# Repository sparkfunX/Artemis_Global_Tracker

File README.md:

# Artemis Global Tracker

An open source global satellite tracker utilising the [SparkFun Artemis module](https://www.sparkfun.com/products/15484),
[Iridium 9603N satellite transceiver](https://www.iridium.com/products/iridium-9603/) and [u-blox ZOE-M8Q GNSS](https://www.u-blox.com/en/product/zoe-m8-series).

[*SparkX Artemis Global Tracker (SPX-16469)*](https://www.sparkfun.com/products/16469)

[*SparkX Artemis Global Tracker (SPX-16469)*](https://www.sparkfun.com/products/16469)

## Retired Product

The SparkX Artemis Global Tracker (SPX-16469) has been replaced by the [SparkFun Artemis Global Tracker (WRL-18712)](https://www.sparkfun.com/products/18712).

## Repository Contents

- **/Documentation** - Documentation for the hardware and the full GlobalTracker example
- **/Hardware** - Eagle PCB, SCH and LBR design files
- **/Software** - Arduino examples
- **/Tools** - Tools to help: configure the full GlobalTracker example via USB or remotely via Iridium messaging; and track and map its position
- **/binaries** - binary files for the examples which you can upload using the [Artemis Firmware Upload GUI](https://github.com/sparkfun/Artemis-Firmware-Upload-GUI) instead of the Arduino IDE
- **LICENSE.md** contains the licence information

## Documentation

- [Hardware overview](Documentation/Hardware_Overview/README.md): an overview of the hardware
- The Artemis pin allocation is summarised [here](Documentation/Hardware_Overview/ARTEMIS_PINS.md)
- [Message Format](Documentation/Message_Format/README.md): a definition of the message format and fields (both binary and text) for the full GlobalTracker example
- [GlobalTracker FAQs](Documentation/GlobalTracker_FAQs/README.md): information to help you operate and configure the AGT

## License Information

This product is _**open source**_!

Please review the LICENSE.md file for license information.

If you have any questions or concerns on licensing, please contact technical support on our [SparkFun forums](https://forum.sparkfun.com/viewforum.php?f=123).

Distributed as-is; no warranty is given.

- Your friends at SparkFun.

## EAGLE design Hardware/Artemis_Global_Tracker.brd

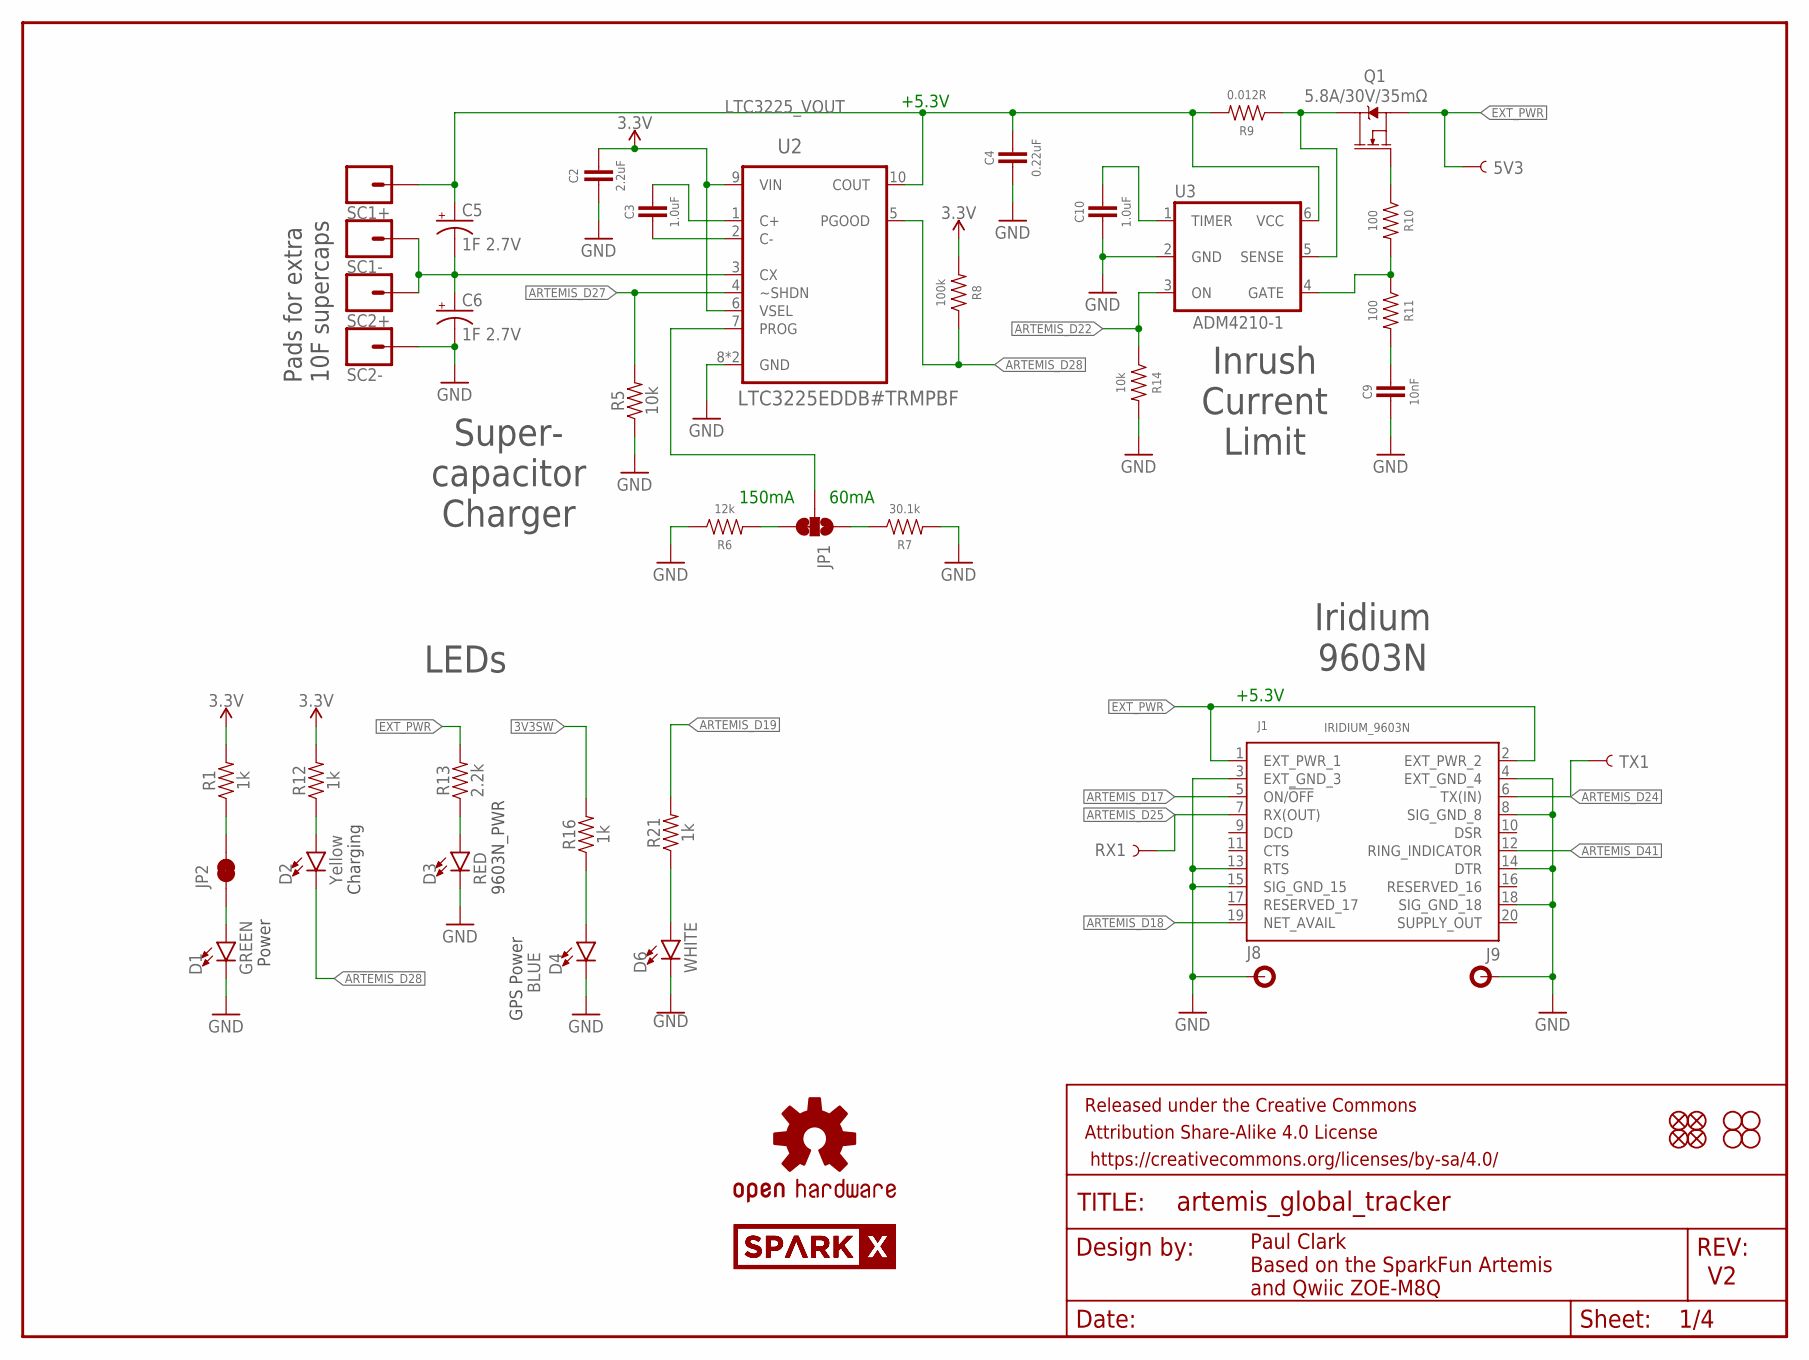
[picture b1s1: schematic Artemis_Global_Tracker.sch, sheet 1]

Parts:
5V3: TEST-POINT3X5; PAD.03X.05
C2: 2.2uF; 0603
C3, C10: 1.0uF; 0603
C4: 0.22uF; 0603
C5, C6: 1F 2.7V; CPOL-RADIAL-1F-2.7V
C9: 10nF; 0603
D1: GREEN; LED-0603
D2: Yellow; LED-0603
D3: RED; LED-0603
D4: BLUE; LED-0603
D6: WHITE; LED-0603
FRAME1: FRAME-LETTER; CREATIVE_COMMONS
J1: IRIDIUM_9603N
J8, J9: STANDOFFS_M2X0.4_STEEL_6MM; STANDOFF_M2X0.4
JP1: JUMPER-SMT_3_1-NC_TRACE_SILK; SMT-JUMPER_3_1-NC_TRACE_SILK
JP2: JUMPER-SMT_2_NC_TRACE_SILK; SMT-JUMPER_2_NC_TRACE_SILK
JP7, JP8, JP13, JP14: FIDUCIAL1X2; FIDUCIAL-1X2
JP9, JP10, JP11, JP12: STAND-OFF
LOGO4: OSHW-LOGOMINI; OSHW-LOGO-MINI
Q1: 5.8A/30V/35mΩ; SOT23-3
R1, R12, R16, R21: 1k; 0603
R5, R14: 10k; 0603
R6: 12k; 0603
R7: 30.1k; 0603
R8: 100k; 0603
R9: 0.012R; 0603
R10, R11: 100; 0603
R13: 2.2k; 0603
RX1: TEST-POINT3X5; PAD.03X.05
SC1+, SC1-, SC2+, SC2-: CONN_01PTH_NO_SILK_YES_STOP; 1X01_NO_SILK
SPARKX1, SPARKX2: SPARKX-LOGO4; SPARKX-MEDIUM
TX1: TEST-POINT3X5; PAD.03X.05
U2: LTC3225EDDB#TRMPBF; DFN300X200-10L
U3: ADM4210-1; TSOT6

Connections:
3.3V: C2.1, R1.2, R8.2, R12.2, U2.6 (VSEL), U2.9 (VIN); also elsewhere on the board
3V3SW: R16.2; also elsewhere on the board
ARTEMIS_D17: J1.5 (ON/!OFF!); also elsewhere on the board
ARTEMIS_D18: J1.19 (NET_AVAIL); also elsewhere on the board
ARTEMIS_D19: R21.2; also elsewhere on the board
ARTEMIS_D22: R14.1, U3.3 (ON); also elsewhere on the board
ARTEMIS_D24: J1.6 (TX(IN)), TX1.P$1; also elsewhere on the board
ARTEMIS_D25: J1.7 (RX(OUT)), RX1.P$1; also elsewhere on the board
ARTEMIS_D27: R5.2, U2.4 (~SHDN); also elsewhere on the board
ARTEMIS_D28: D2.C, R8.1, U2.5 (PGOOD); also elsewhere on the board
ARTEMIS_D41: J1.12 (RING_INDICATOR); also elsewhere on the board
EXT_PWR: 5V3.P$1, J1.1 (EXT_PWR_1), J1.2 (EXT_PWR_2), Q1.2 (S), R13.2; also elsewhere on the board
GND: C2.2, C4.2, C6.-, C9.2, C10.2, D1.C, D3.C, D4.C, D6.C, J1.3 (EXT_GND_3), J1.4 (EXT_GND_4), J1.8 (SIG_GND_8), J1.13 (RTS), J1.14 (DTR), J1.15 (SIG_GND_15), J1.18 (SIG_GND_18), J8.1, J9.1, R5.1, R6.1, R7.2, R14.2, SC2-.1, U2.8 (GND), U2.11 (GND), U3.2 (GND); also elsewhere on the board
LTC3225_VOUT: C4.1, C5.+, R9.2, SC1+.1, U2.10 (COUT), U3.6 (VCC)
unnamed: C5.-, C6.+, SC1-.1, SC2+.1, U2.3 (CX)
unnamed: JP1.3, R6.2
unnamed: JP2.2, R1.1
unnamed: JP1.1, R7.1
unnamed: D2.A, R12.1
unnamed: D3.A, R13.1
unnamed: Q1.3 (D), R9.1, U3.5 (SENSE)
unnamed: C3.2, U2.2 (C-)
unnamed: C3.1, U2.1 (C+)
unnamed: JP1.2, U2.7 (PROG)
unnamed: Q1.1 (G), R10.1
unnamed: R10.2, R11.1, U3.4 (GATE)
unnamed: C9.1, R11.2
unnamed: C10.1, U3.1 (TIMER)
unnamed: D4.A, R16.1
unnamed: D1.A, JP2.1
unnamed: D6.A, R21.1

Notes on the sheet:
Paul Clark Based on the SparkFun Artemis and Qwiic ZOE-M8Q
Power
+5.3V
150mA
60mA
Pads for extra 10F supercaps
Super- capacitor Charger
Charging
9603N_PWR
Iridium 9603N
LEDs
Inrush Current Limit
GPS Power

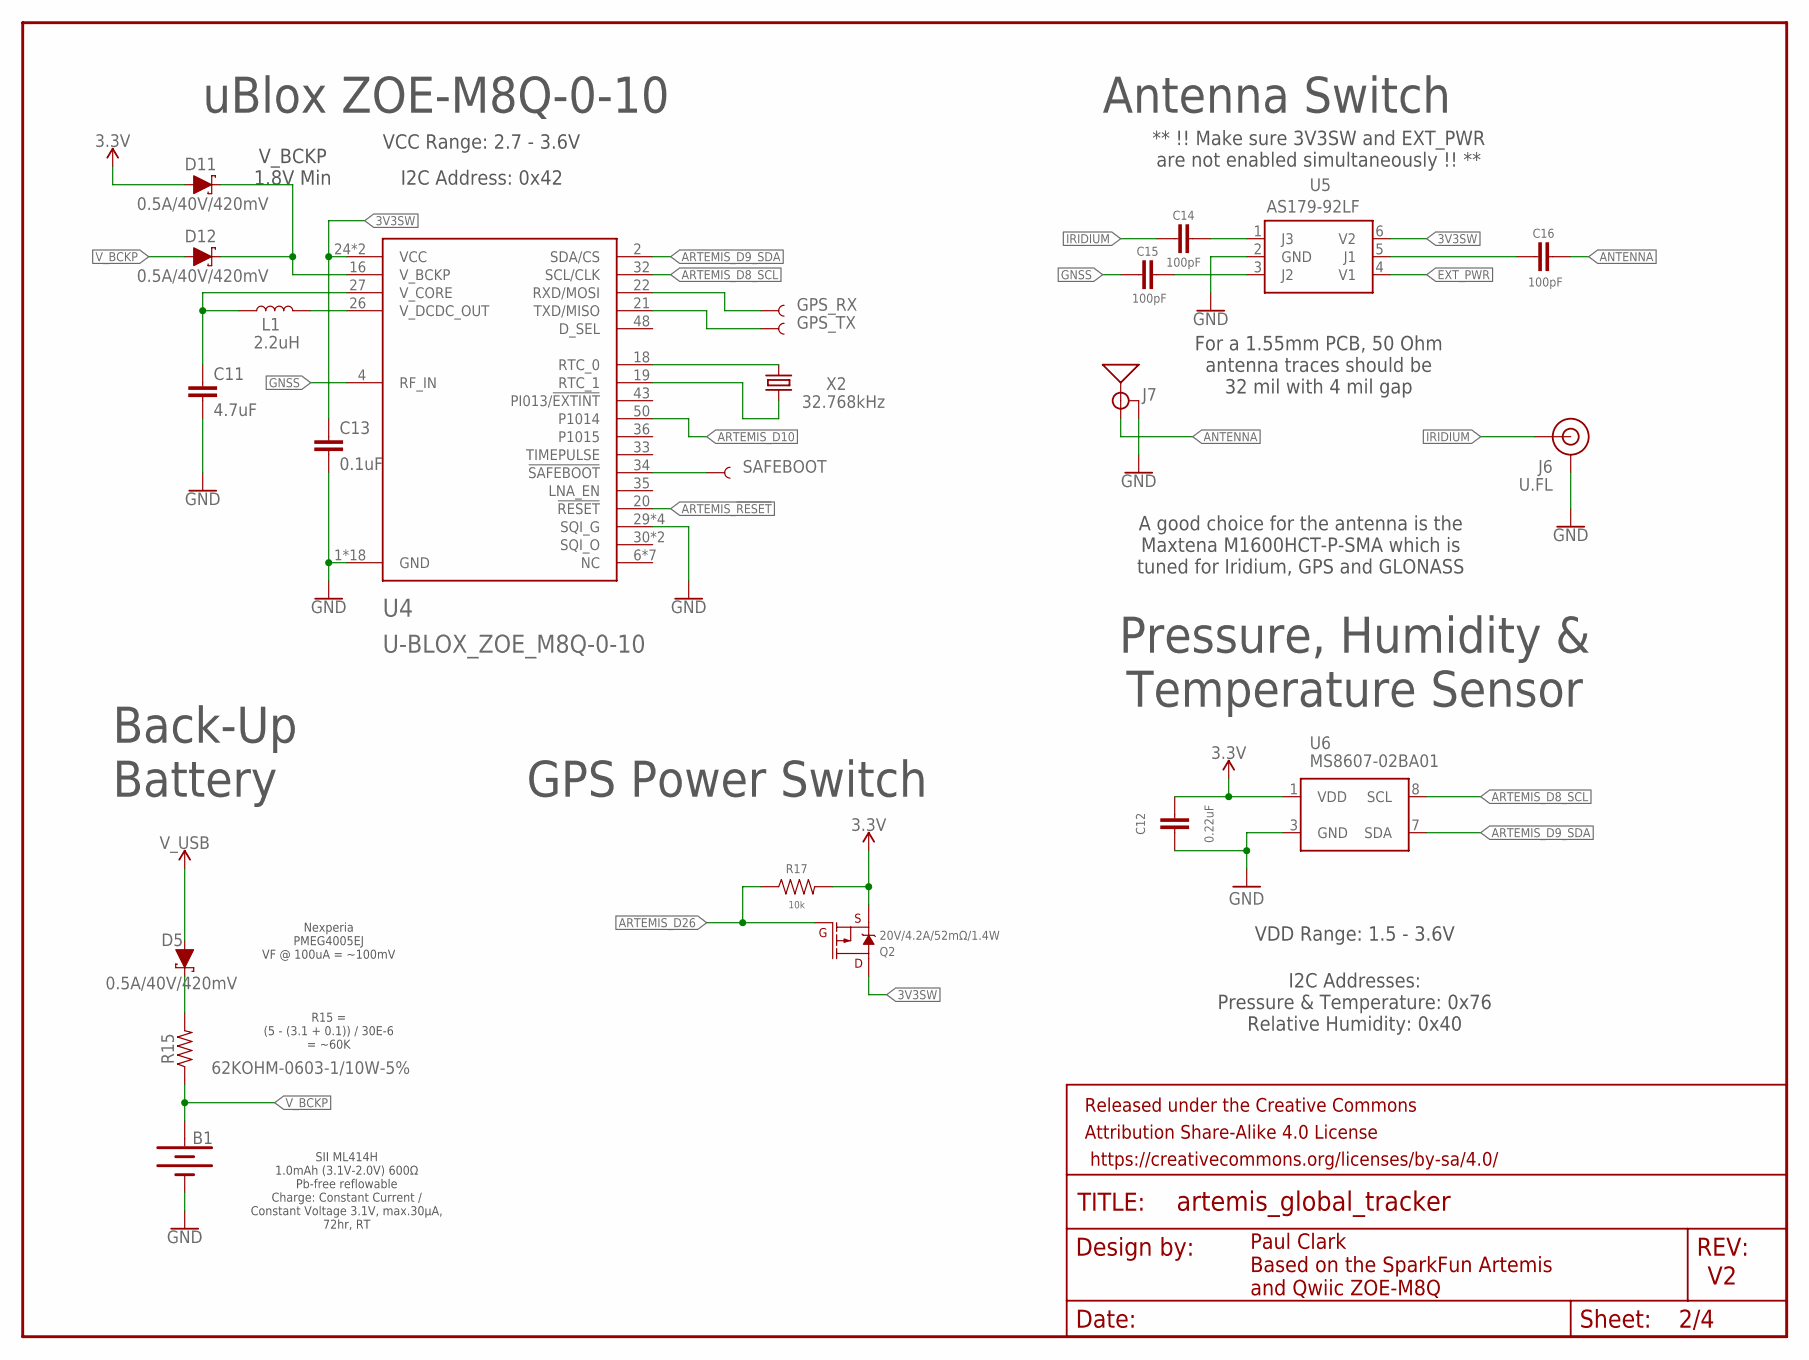
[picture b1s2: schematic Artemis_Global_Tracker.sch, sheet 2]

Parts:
B1: ML414H_IV01E_BATTERY; ML414H_IV01E
C11: 4.7uF; 0603
C12: 0.22uF; 0603
C13: 0.1uF; 0603
C14, C15, C16: 100pF; 0603
D5, D11, D12: 0.5A/40V/420mV; SOD-323
FRAME2: FRAME-LETTER; CREATIVE_COMMONS
GPS_RX: TEST-POINT3X5; PAD.03X.05
GPS_TX: TEST-POINT3X5; PAD.03X.05
J6: U.FL
J7: ANTENNA-GROUNDEDEDGE_SMA; SMA-EDGE
L1: 2.2uH; 0806
Q2: 20V/4.2A/52mΩ/1.4W; SOT23-3
R15: 62KOHM-0603-1/10W-5%; 0603
R17: 10k; 0603
SAFEBOOT: TEST-POINT3X5; PAD.03X.05
U4: U-BLOX_ZOE_M8Q-0-10; UBLOX_ZOE_M8-0-10
U5: AS179-92LF; SOT65P220X100-6N
U6: MS8607-02BA01
X2: 32.768kHz; CRYSTAL-SMD-3.2X1.5MM

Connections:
3.3V: C12.1, D11.A, Q2.2 (S), R17.2, U6.1 (VDD); also elsewhere on the board
3V3SW: C13.1, Q2.3 (D), U4.24 (VCC), U4.25 (VCC), U5.6 (V2); also elsewhere on the board
ANTENNA: C16.1, J7.SIG (SIGNAL)
ARTEMIS_!RESET: U4.20 (!RESET); also elsewhere on the board
ARTEMIS_D8_SCL: U4.32 (SCL/CLK), U6.8 (SCL); also elsewhere on the board
ARTEMIS_D9_SDA: U4.2 (SDA/CS), U6.7 (SDA); also elsewhere on the board
ARTEMIS_D10: U4.50 (P1014); also elsewhere on the board
ARTEMIS_D26: Q2.1 (G), R17.1; also elsewhere on the board
EXT_PWR: U5.4 (V1); also elsewhere on the board
GND: B1.-, C11.2, C12.2, C13.2, J6.1 (GND), J6.2 (GND), J7.GND@0 (GND), J7.GND@1 (GND), J7.GND@2 (GND), J7.GND@3 (GND), U4.1 (GND), U4.3 (GND), U4.5 (GND), U4.7 (GND), U4.8 (GND), U4.9 (GND), U4.10 (GND), U4.11 (GND), U4.12 (GND), U4.17 (GND), U4.23 (GND), U4.29 (SQI_G), U4.31 (SQI_G), U4.37 (GND), U4.38 (GND), U4.39 (GND), U4.40 (GND), U4.41 (GND), U4.44 (GND), U4.46 (SQI_G), U4.47 (SQI_G), U4.49 (GND), U5.2 (GND), U6.3 (GND); also elsewhere on the board
GNSS: C15.2, U4.4 (RF_IN)
IRIDIUM: C14.2, J6.FEED (SIGNAL)
unnamed: L1.2, U4.26 (V_DCDC_OUT)
unnamed: C11.1, L1.1, U4.27 (V_CORE)
unnamed: U4.18 (RTC_0), X2.P$2 (2)
unnamed: U4.19 (RTC_1), X2.P$1 (1)
unnamed: D5.C, R15.2
unnamed: D11.C, D12.C, U4.16 (V_BCKP)
unnamed: SAFEBOOT.P$1, U4.34 (!SAFEBOOT)
unnamed: GPS_RX.P$1, U4.22 (RXD/MOSI)
unnamed: GPS_TX.P$1, U4.21 (TXD/MISO)
unnamed: C14.1, U5.1 (J3)
unnamed: C15.1, U5.3 (J2)
unnamed: C16.2, U5.5 (J1)
V_BCKP: B1.+, D12.A, R15.1
V_USB: D5.A; also elsewhere on the board

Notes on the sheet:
Paul Clark Based on the SparkFun Artemis and Qwiic ZOE-M8Q
uBlox ZOE-M8Q-0-10
Back-Up Battery
Antenna Switch
SII ML414H 1.0mAh (3.1V-2.0V) 600Ω Pb-free reflowable Charge: Constant Current / Constant Voltage 3.1V, max.30μA, 72hr, RT
VCC Range: 2.7 - 3.6V
I2C Address: 0x42
GPS Power Switch
Pressure, Humidity & Temperature Sensor
VDD Range: 1.5 - 3.6V
I2C Addresses: Pressure & Temperature: 0x76 Relative Humidity: 0x40
** !! Make sure 3V3SW and EXT_PWR are not enabled simultaneously !! **
A good choice for the antenna is the Maxtena M1600HCT-P-SMA which is tuned for Iridium, GPS and GLONASS
For a 1.55mm PCB, 50 Ohm antenna traces should be 32 mil with 4 mil gap
Nexperia PMEG4005EJ VF @ 100uA = ~100mV
R15 = (5 - (3.1 + 0.1)) / 30E-6 = ~60K
V_BCKP 1.8V Min

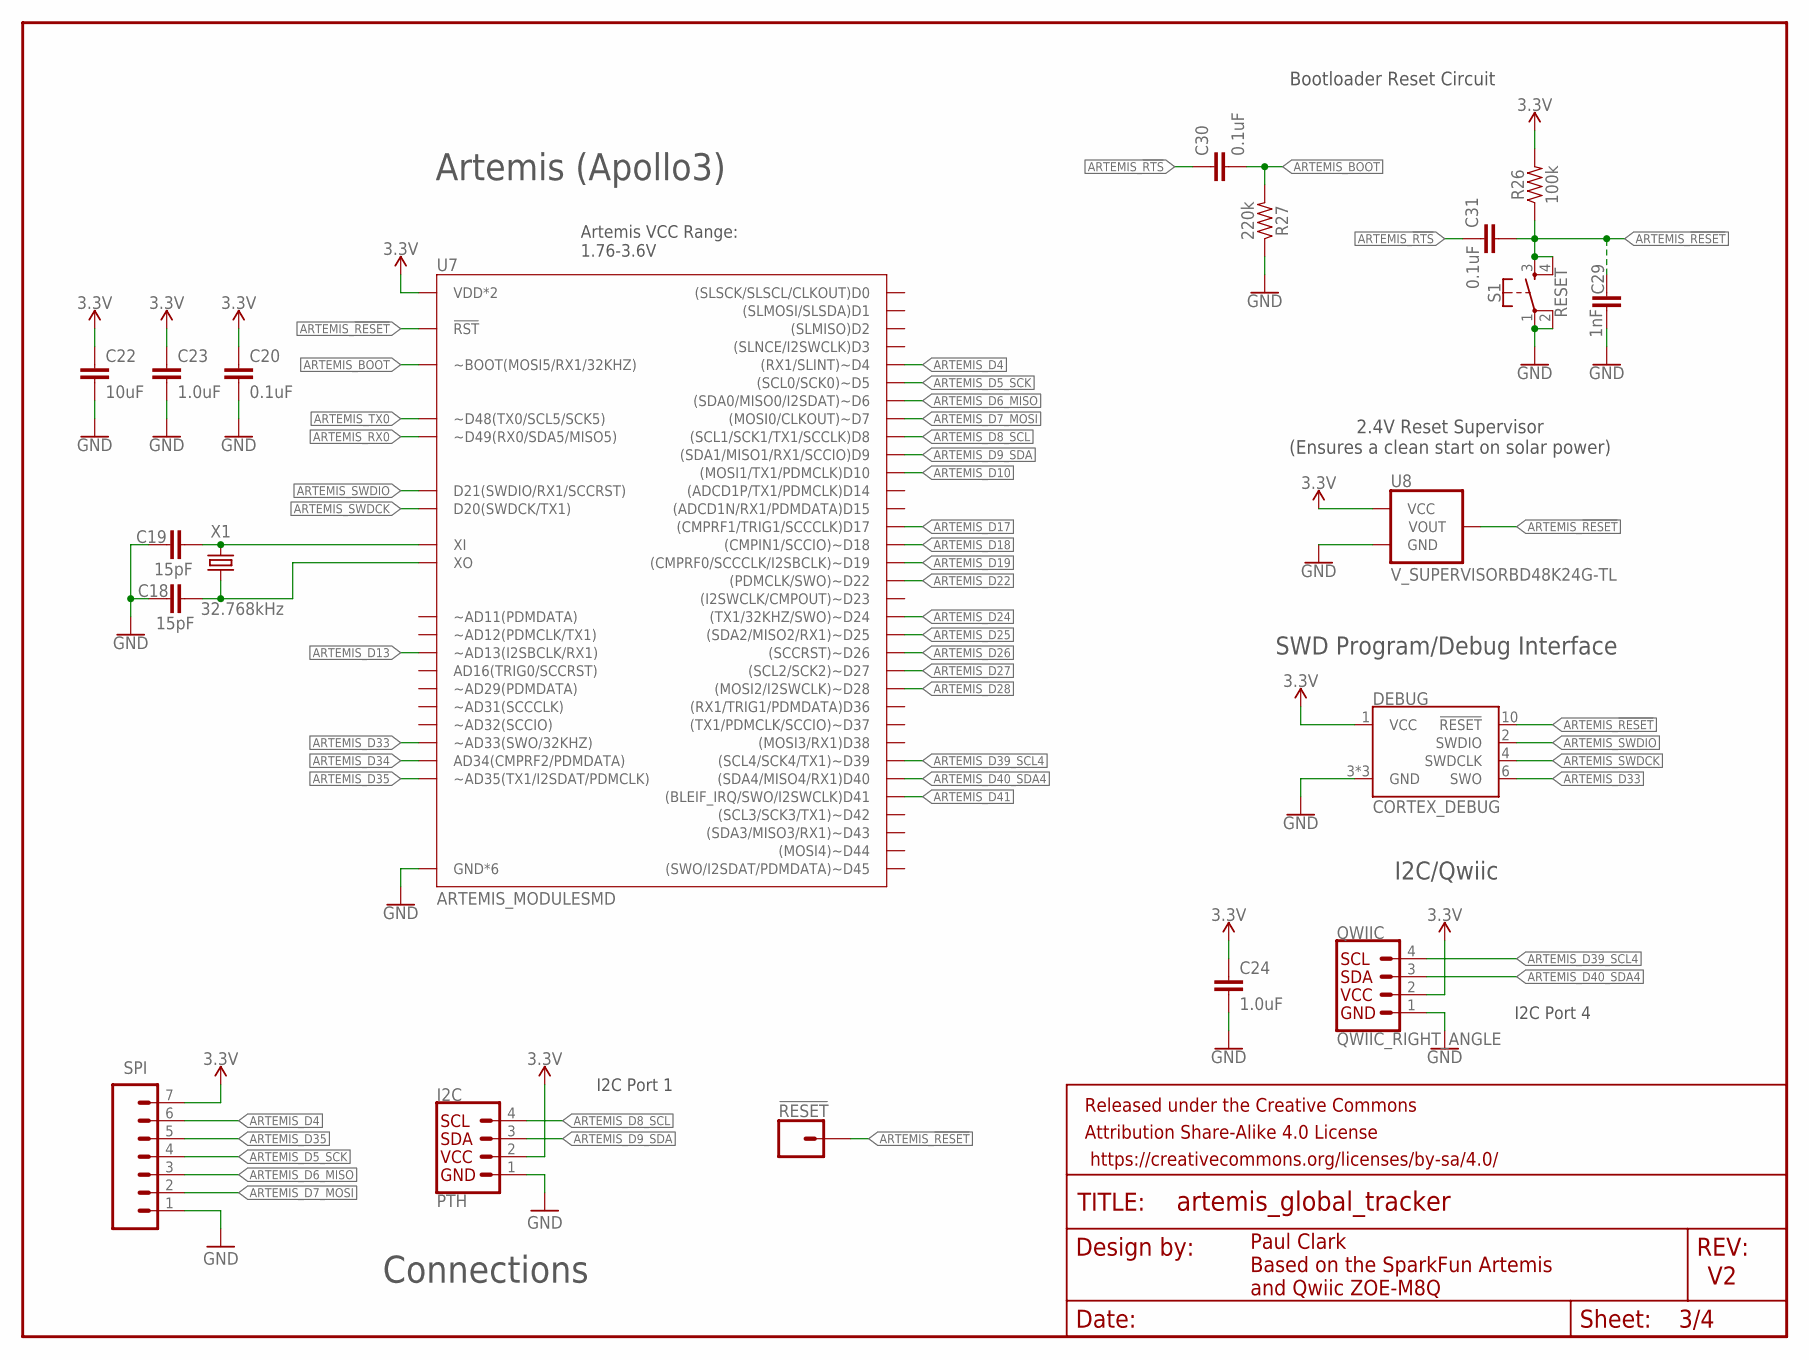
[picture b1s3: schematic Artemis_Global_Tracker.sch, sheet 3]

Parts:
!RESET: CONN_01PTH_NO_SILK_YES_STOP; 1X01_NO_SILK
C18, C19: 15pF; 0603
C20, C30, C31: 0.1uF; 0603
C22: 10uF; 0603
C23, C24: 1.0uF; 0603
C29: 1nF; 0603
DEBUG: CORTEX_DEBUG; 2X5-PTH-1.27MM-NO_SILK
FRAME3: FRAME-LETTER; CREATIVE_COMMONS
I2C: PTH; 1X04_NO_SILK
QWIIC: QWIIC_RIGHT_ANGLE; JST04_1MM_RA
R26: 100k; 0603
R27: 220k; 0603
S1: RESET; TACTILE_SWITCH_SMD_5.2MM
SPI: CONN_07NO_SILK; 1X07_NO_SILK
U7: ARTEMIS_MODULESMD; ARTEMIS_FP
U8: V_SUPERVISORBD48K24G-TL; SSOP3
X1: 32.768kHz; CRYSTAL-SMD-3.2X1.5MM

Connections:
3.3V: C20.2, C22.1, C23.1, C24.1, DEBUG.1 (VCC), I2C.2, QWIIC.2, R26.2, SPI.7, U7.VDD@36 (VDD*2), U7.VDD@37 (VDD*2), U8.3 (VCC); also elsewhere on the board
ARTEMIS_!RESET: !RESET.1, C29.1, C31.2, DEBUG.10 (!RESET), R26.1, S1.3, S1.4, U7.~RST (!RST), U8.2 (VOUT); also elsewhere on the board
ARTEMIS_!RTS!: C30.1, C31.1; also elsewhere on the board
ARTEMIS_BOOT: C30.2, R27.2, U7.BOOT (~BOOT(MOSI5/RX1/32KHZ))
ARTEMIS_D4: SPI.6, U7.~D4 ((RX1/SLINT)~D4)
ARTEMIS_D5_SCK: SPI.4, U7.~D5 ((SCL0/SCK0)~D5)
ARTEMIS_D6_MISO: SPI.3, U7.~D6 ((SDA0/MISO0/I2SDAT)~D6)
ARTEMIS_D7_MOSI: SPI.2, U7.D7 ((MOSI0/CLKOUT)~D7)
ARTEMIS_D8_SCL: I2C.4, U7.D8 ((SCL1/SCK1/TX1/SCCLK)D8); also elsewhere on the board
ARTEMIS_D9_SDA: I2C.3, U7.D9 ((SDA1/MISO1/RX1/SCCIO)D9); also elsewhere on the board
ARTEMIS_D10: U7.D10 ((MOSI1/TX1/PDMCLK)D10); also elsewhere on the board
ARTEMIS_D13: U7.~AD13 (~AD13(I2SBCLK/RX1)); also elsewhere on the board
ARTEMIS_D17: U7.D17 ((CMPRF1/TRIG1/SCCCLK)D17); also elsewhere on the board
ARTEMIS_D18: U7.~D18 ((CMPIN1/SCCIO)~D18); also elsewhere on the board
ARTEMIS_D19: U7.~D19 ((CMPRF0/SCCCLK/I2SBCLK)~D19); also elsewhere on the board
ARTEMIS_D22: U7.~D22 ((PDMCLK/SWO)~D22); also elsewhere on the board
ARTEMIS_D24: U7.~D24 ((TX1/32KHZ/SWO)~D24); also elsewhere on the board
ARTEMIS_D25: U7.~D25 ((SDA2/MISO2/RX1)~D25); also elsewhere on the board
ARTEMIS_D26: U7.~D26 ((SCCRST)~D26); also elsewhere on the board
ARTEMIS_D27: U7.~D27 ((SCL2/SCK2)~D27); also elsewhere on the board
ARTEMIS_D28: U7.~D28 ((MOSI2/I2SWCLK)~D28); also elsewhere on the board
ARTEMIS_D33: DEBUG.6 (SWO), U7.~AD33/SWO (~AD33(SWO/32KHZ))
ARTEMIS_D34: U7.AD34 (AD34(CMPRF2/PDMDATA)); also elsewhere on the board
ARTEMIS_D35: SPI.5, U7.~AD35 (~AD35(TX1/I2SDAT/PDMCLK))
ARTEMIS_D39_SCL4: QWIIC.4, U7.~D39 ((SCL4/SCK4/TX1)~D39)
ARTEMIS_D40_SDA4: QWIIC.3, U7.D40 ((SDA4/MISO4/RX1)D40)
ARTEMIS_D41: U7.D41 ((BLEIF_IRQ/SWO/I2SWCLK)D41); also elsewhere on the board
ARTEMIS_RX0: U7.RXI-0 (~D49(RX0/SDA5/MISO5)); also elsewhere on the board
ARTEMIS_SWDCK: DEBUG.4 (SWDCLK), U7.SWDCK (D20(SWDCK/TX1))
ARTEMIS_SWDIO: DEBUG.2 (SWDIO), U7.SWDIO (D21(SWDIO/RX1/SCCRST))
ARTEMIS_TX0: U7.TXO-0 (~D48(TX0/SCL5/SCK5)); also elsewhere on the board
GND: C18.1, C19.1, C20.1, C22.2, C23.2, C24.2, C29.2, DEBUG.3 (GND), DEBUG.5 (GND), DEBUG.9 (GND), I2C.1, QWIIC.1, R27.1, S1.1, S1.2, SPI.1, U7.GND@1 (GND*6), U7.GND@22 (GND*6), U7.GND@38 (GND*6), U7.GND@39 (GND*6), U7.GND@47 (GND*6), U7.GND@59 (GND*6), U8.1 (GND); also elsewhere on the board
XTALI: C19.2, U7.XI, X1.P$1 (1)
XTALO: C18.2, U7.XO, X1.P$2 (2)

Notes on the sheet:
Paul Clark Based on the SparkFun Artemis and Qwiic ZOE-M8Q
Artemis (Apollo3)
Artemis VCC Range: 1.76-3.6V
Bootloader Reset Circuit
SWD Program/Debug Interface
I2C/Qwiic
Connections
I2C Port 1
I2C Port 4
2.4V Reset Supervisor (Ensures a clean start on solar power)

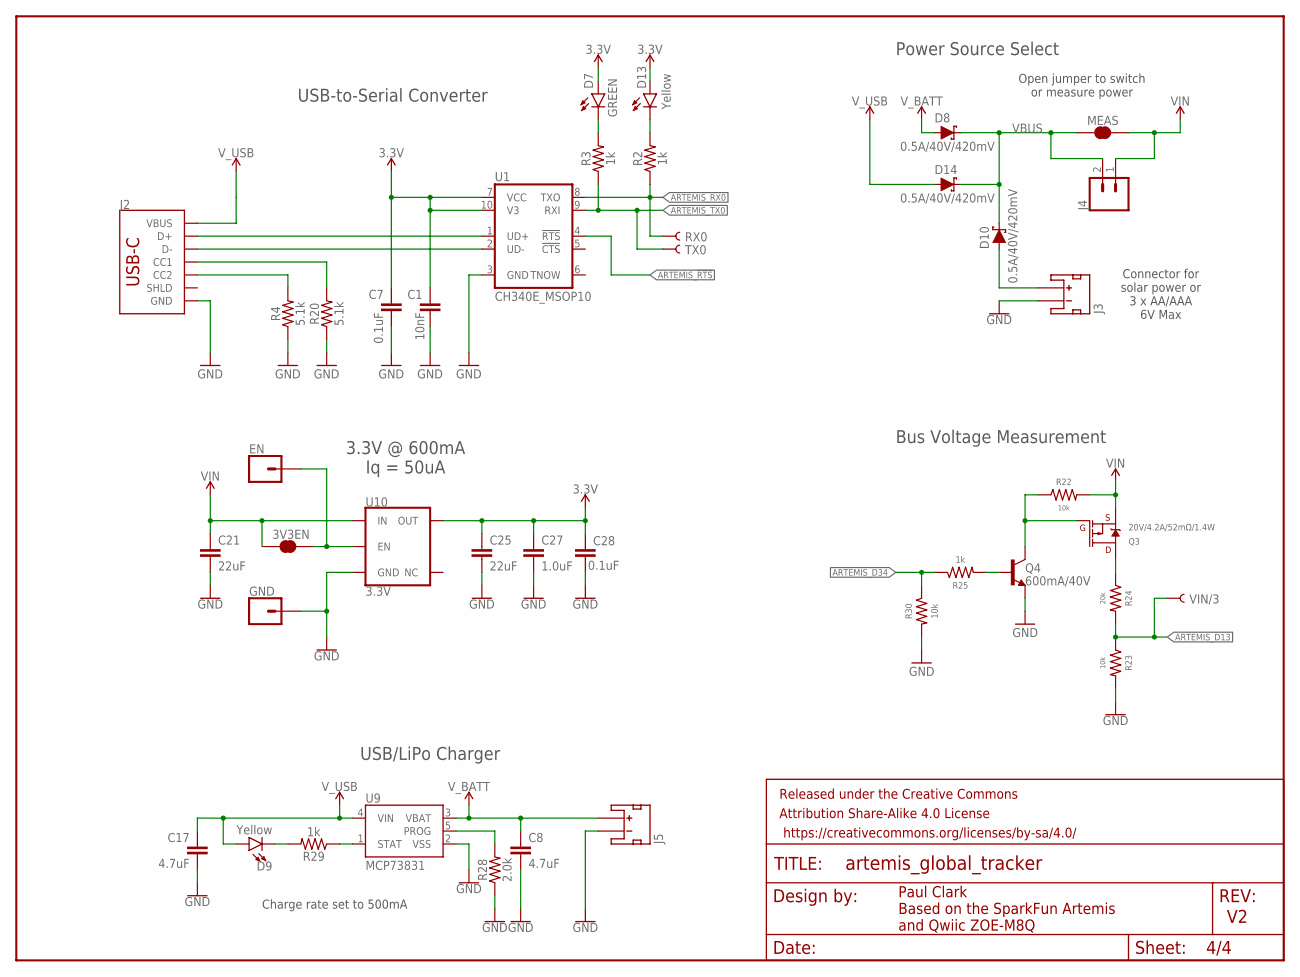
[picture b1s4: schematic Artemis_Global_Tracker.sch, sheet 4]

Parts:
3V3EN: JUMPER-SMT_2_NC_TRACE_SILK; SMT-JUMPER_2_NC_TRACE_SILK
C1: 10nF; 0603
C7, C28: 0.1uF; 0603
C8, C17: 4.7uF; 0603
C21: 22uF; 0805
C25: 22uF; 0603
C27: 1.0uF; 0603
D7: GREEN; LED-0603
D8, D10, D14: 0.5A/40V/420mV; SOD-323
D9, D13: Yellow; LED-0603
EN: CONN_01PTH_NO_SILK_YES_STOP; 1X01_NO_SILK
FRAME4: FRAME-LETTER; CREATIVE_COMMONS
GND: CONN_01PTH_NO_SILK_YES_STOP; 1X01_NO_SILK
J2: USB-C; USB-C-16P
J3, J5: JST_2MM_MALE; JST-2-SMD
J4: CONN_021X02_NO_SILK; 1X02_NO_SILK
MEAS: JUMPER-SMT_2_NC_TRACE_SILK; SMT-JUMPER_2_NC_TRACE_SILK
Q3: 20V/4.2A/52mΩ/1.4W; SOT23-3
Q4: 600mA/40V; SOT23-3
R2, R3, R25, R29: 1k; 0603
R4, R20: 5.1k; 0603
R22, R23, R30: 10k; 0603
R24: 20k; 0603
R28: 2.0k; 0603
RX0: TEST-POINT3X5; PAD.03X.05
TX0: TEST-POINT3X5; PAD.03X.05
U1: CH340E_MSOP10; MSOP10
U9: MCP73831; SOT23-5
U10: 3.3V; SOT23-5
VIN/3: TEST-POINT3X5; PAD.03X.05

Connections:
3.3V: C1.1, C7.1, C25.1, C27.1, C28.1, D7.A, D13.A, U1.7 (VCC), U1.10 (V3), U10.5 (OUT); also elsewhere on the board
ARTEMIS_!RTS!: U1.4 (!RTS); also elsewhere on the board
ARTEMIS_D13: R23.1, R24.2, VIN/3.P$1; also elsewhere on the board
ARTEMIS_D34: R25.1, R30.1; also elsewhere on the board
ARTEMIS_RX0: R2.1, RX0.P$1, U1.8 (TXO); also elsewhere on the board
ARTEMIS_TX0: R3.1, TX0.P$1, U1.9 (RXI); also elsewhere on the board
CC3: J2.B5 (CC2), R4.2
CC4: J2.A5 (CC1), R20.2
D+2: J2.A6 (D+), J2.B6 (D+), U1.1 (UD+)
D-2: J2.A7 (D-), J2.B7 (D-), U1.2 (UD-)
GND: C1.2, C7.2, C8.2, C17.2, C21.2, C25.2, C27.2, C28.2, GND.1, J2.GND, J2.GND2 (GND), J3.1 (-), J5.1 (-), Q4.2 (E), R4.1, R20.1, R23.2, R28.1, R30.2, U1.3 (GND), U9.2 (VSS), U10.2 (GND); also elsewhere on the board
unnamed: D13.C, R2.2
unnamed: D7.C, R3.2
unnamed: 3V3EN.2, EN.1, U10.3 (EN)
unnamed: Q3.1 (G), Q4.3 (C), R22.1
unnamed: R28.2, U9.5 (PROG)
unnamed: D9.C, R29.2
unnamed: R29.1, U9.1 (STAT)
unnamed: Q3.3 (D), R24.1
unnamed: Q4.1 (B), R25.2
VBUS: D8.C, D10.C, D14.C, J4.2, MEAS.1
VIN: 3V3EN.1, C21.1, J4.1, MEAS.2, Q3.2 (S), R22.2, U10.1 (IN)
V_AAA: D10.A, J3.2 (+)
V_BATT: C8.1, D8.A, J5.2 (+), U9.3 (VBAT)
V_USB: C17.1, D9.A, D14.A, J2.VBUS1 (VBUS), J2.VBUS2 (VBUS), U9.4 (VIN); also elsewhere on the board

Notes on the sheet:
Paul Clark Based on the SparkFun Artemis and Qwiic ZOE-M8Q
3.3V @ 600mA Iq = 50uA
USB/LiPo Charger
Charge rate set to 500mA
Power Source Select
USB-to-Serial Converter
Open jumper to switch or measure power
Connector for solar power or 3 x AA/AAA 6V Max
Bus Voltage Measurement

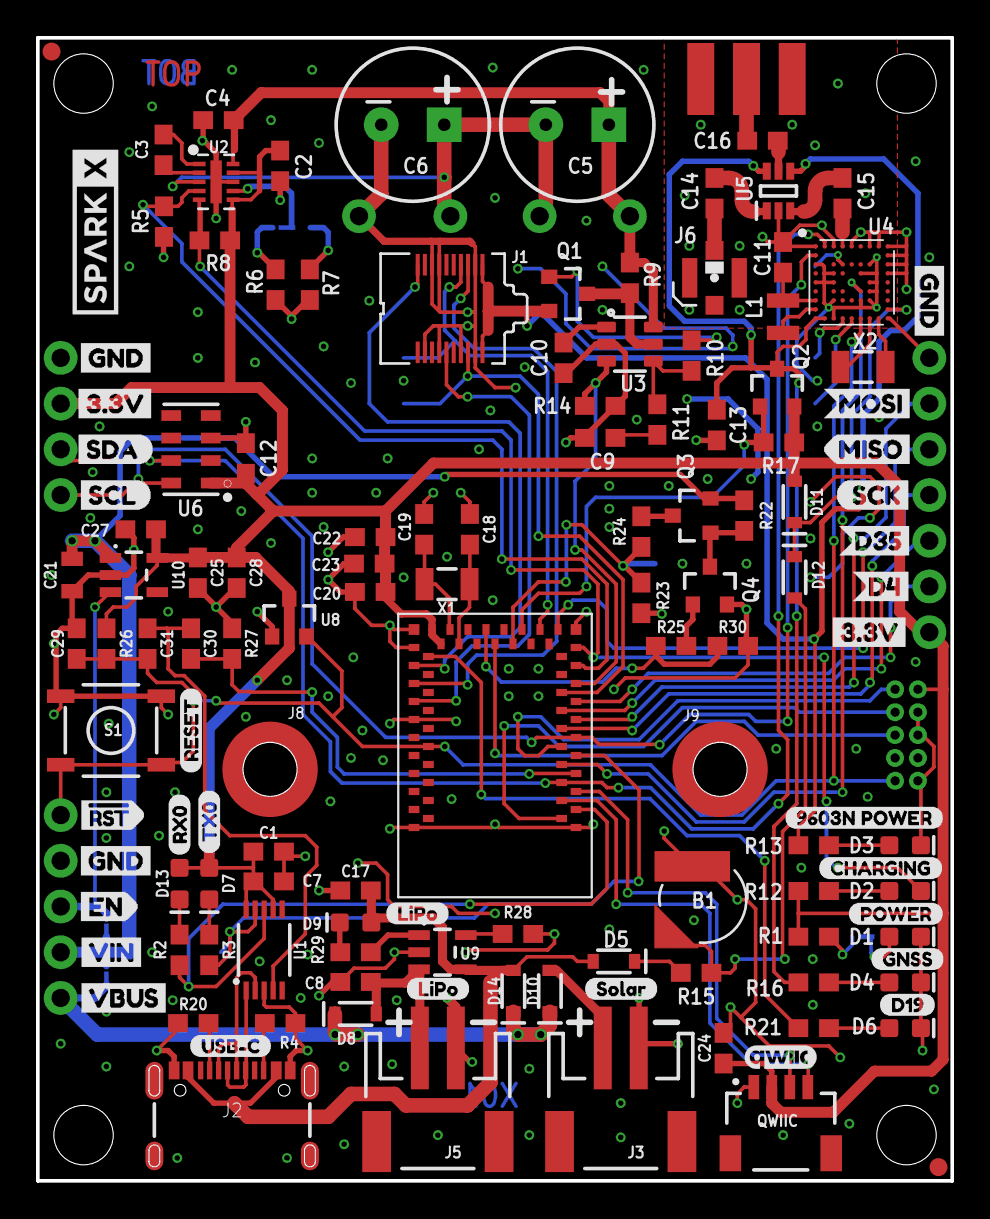
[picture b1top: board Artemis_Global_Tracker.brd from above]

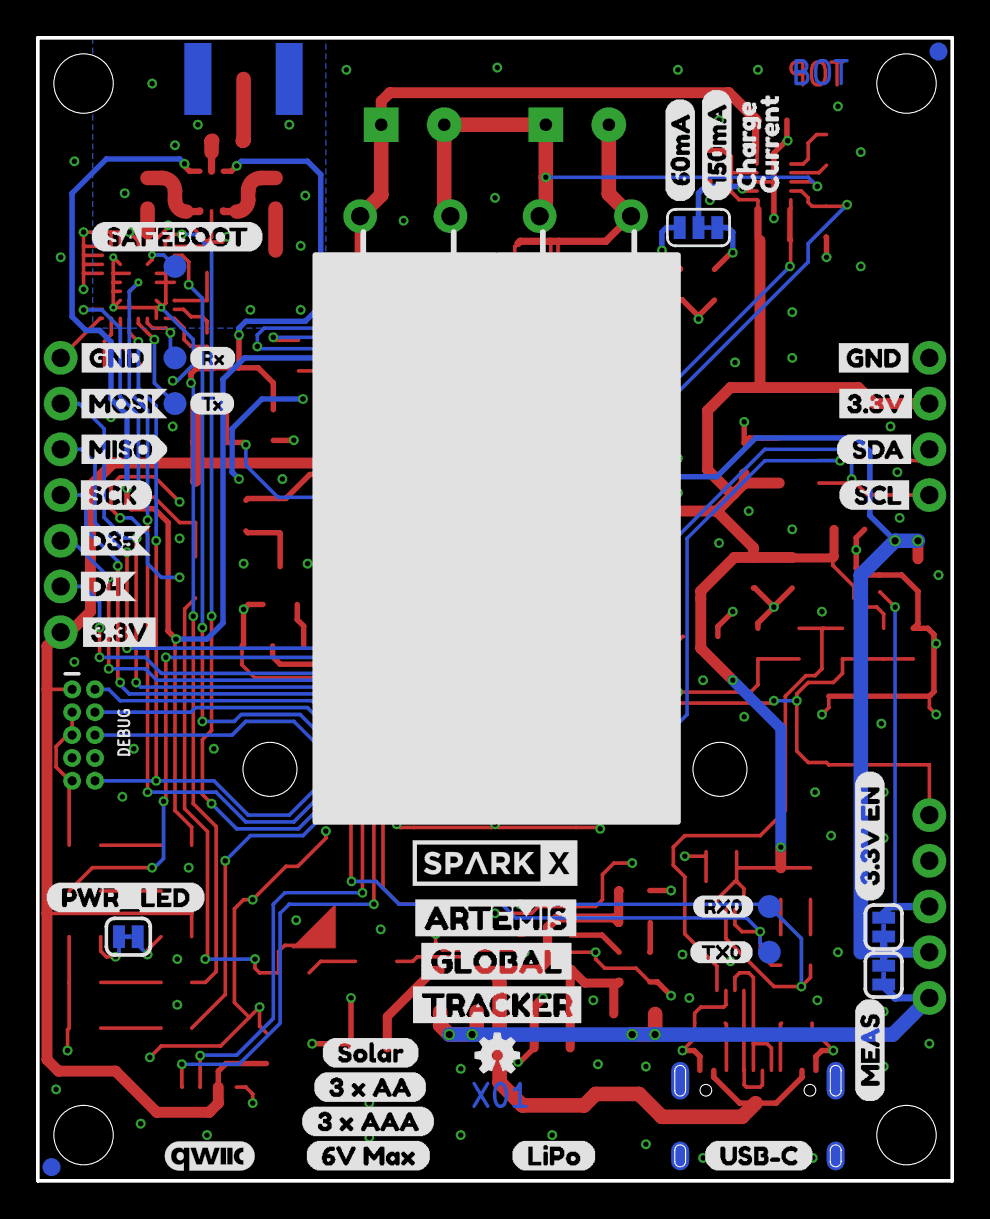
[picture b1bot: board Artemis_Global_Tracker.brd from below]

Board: 2 copper layers, 50.8 x 63.5 mm, 205 parts (55 on the bottom side), 88 nets.

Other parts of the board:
U$1: 60MA0
U$2: POWER0
U$3, U$12, U$17, U$22: GND1
U$4, U$20, U$21, U$24: 3#3V2
U$5: SCL0
U$6: SDA0
U$7: EN0
U$9: CHARGING0
U$10: 9603N_POWER0
U$11: QWIIC_4MM
U$13: 150MA0
U$14: CHARGE0
U$15: CURRENT0
U$16, U$38: TX00
U$18, U$31: SCK0
U$19: GNSS0
U$23, U$34: RX00
U$25: QWIIC_5MM
U$26: SCL9
U$27: SDA8
U$29, U$64: SOLAR0
U$32: 5#3V0
U$33: RX0
U$35: RX10
U$36: SAFEBOOT0
U$37: TX0
U$39: TX10
U$40: ARTEMIS0
U$41: GLOBAL0
U$42: TRACKER0
U$43: PWR_LED0
U$44: VBUS0
U$45, U$46, U$57: LIPO0
U$47: 3#3V_EN0
U$48: MEAS0
U$49: RESET0
U$50: D190
U$53, U$56: USB#C0
U$58: #RST0
U$59: GND0
U$60: VIN0
U$61: 3_X_AA0
U$62: 3_X_AAA0
U$63: 6V_MAX0
U$65: VIN#30
U$67, U$68: D350
U$69, U$70: MISO0
U$71, U$72: MOSI0
U$73, U$74: D40

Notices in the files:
parts and their libraries:
SparkFun-Resistors: Licensing: Creative Commons ShareAlike 4.0 International - https://creativecommons.org/licenses/by-sa/4.0
SparkFun-Aesthetics: Released under the Creative Commons Attribution Share-Alike 4.0 License
SparkFun-Aesthetics: https://creativecommons.org/licenses/by-sa/4.0
